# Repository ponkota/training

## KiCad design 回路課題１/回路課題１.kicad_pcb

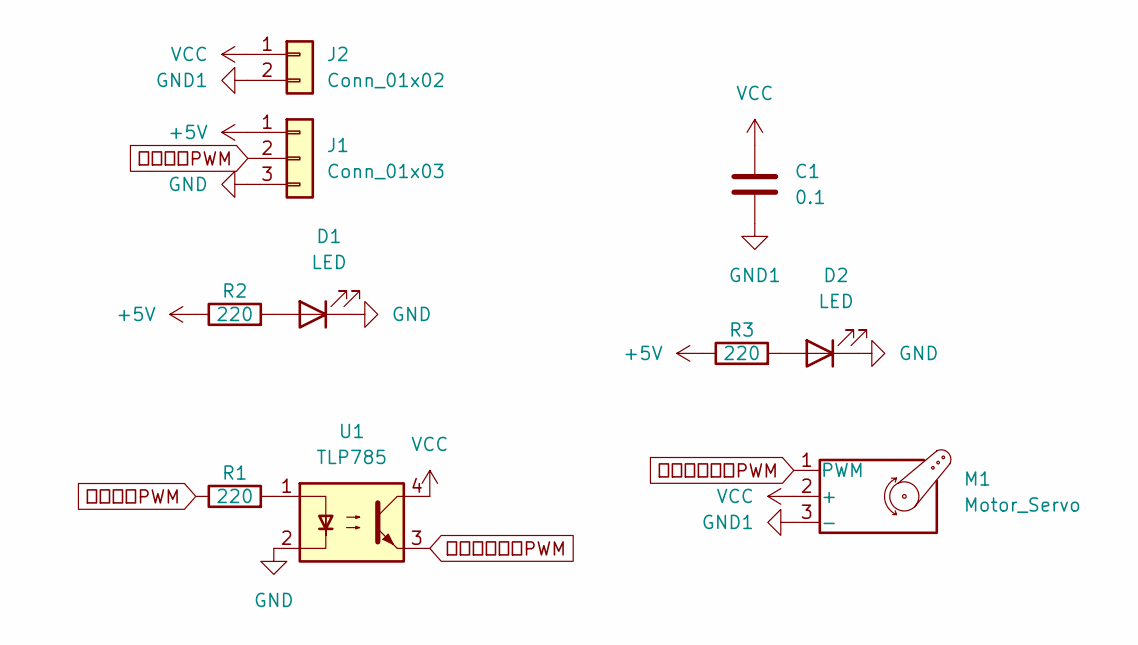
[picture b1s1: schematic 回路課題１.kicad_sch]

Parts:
C1: 0.1; C_Disc_D3.0mm_W1.6mm_P2.50mm
D1, D2: LED; LED_D3.0mm
J1: Conn_01x03; JST_XA_S03B-XASK-1_1x03_P2.50mm_Horizontal
J2: Conn_01x02; AMASS_XT30PW-F_1x02_P2.50mm_Horizontal
M1: Motor_Servo; JST_XA_S03B-XASK-1_1x03_P2.50mm_Horizontal
R1, R2, R3: 220; R_Axial_DIN0207_L6.3mm_D2.5mm_P10.16mm_Horizontal
U1: TLP785; DIP-4_W7.62mm

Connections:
+5V: J1.1, R2.1, R3.1
GND: D1.1 (K), D2.1 (K), J1.3, U1.2
GND1: C1.2, J2.2, M1.3 (-)
unnamed: D1.2 (A), R2.2
unnamed: D2.2 (A), R3.2
unnamed: R1.2, U1.1
VCC: C1.1, J2.1, M1.2 (+), U1.4
フォトカプラPWM: M1.1 (PWM), U1.3
マイコンPWM: J1.2, R1.1

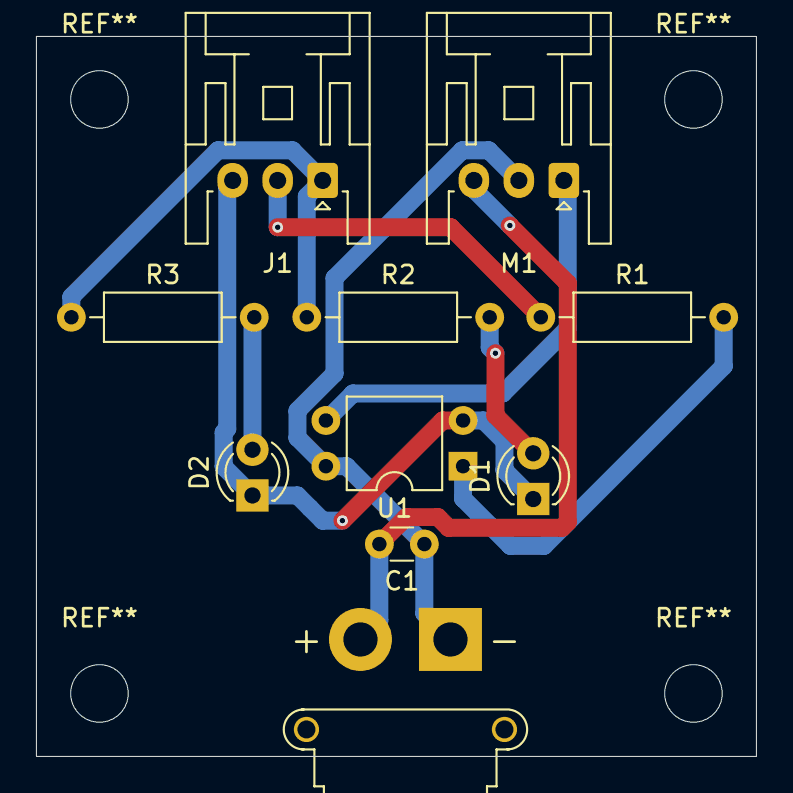
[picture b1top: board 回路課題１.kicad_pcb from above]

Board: 2 copper layers, 40.0 x 40.0 mm, 10 parts (0 on the bottom side), 9 nets.
